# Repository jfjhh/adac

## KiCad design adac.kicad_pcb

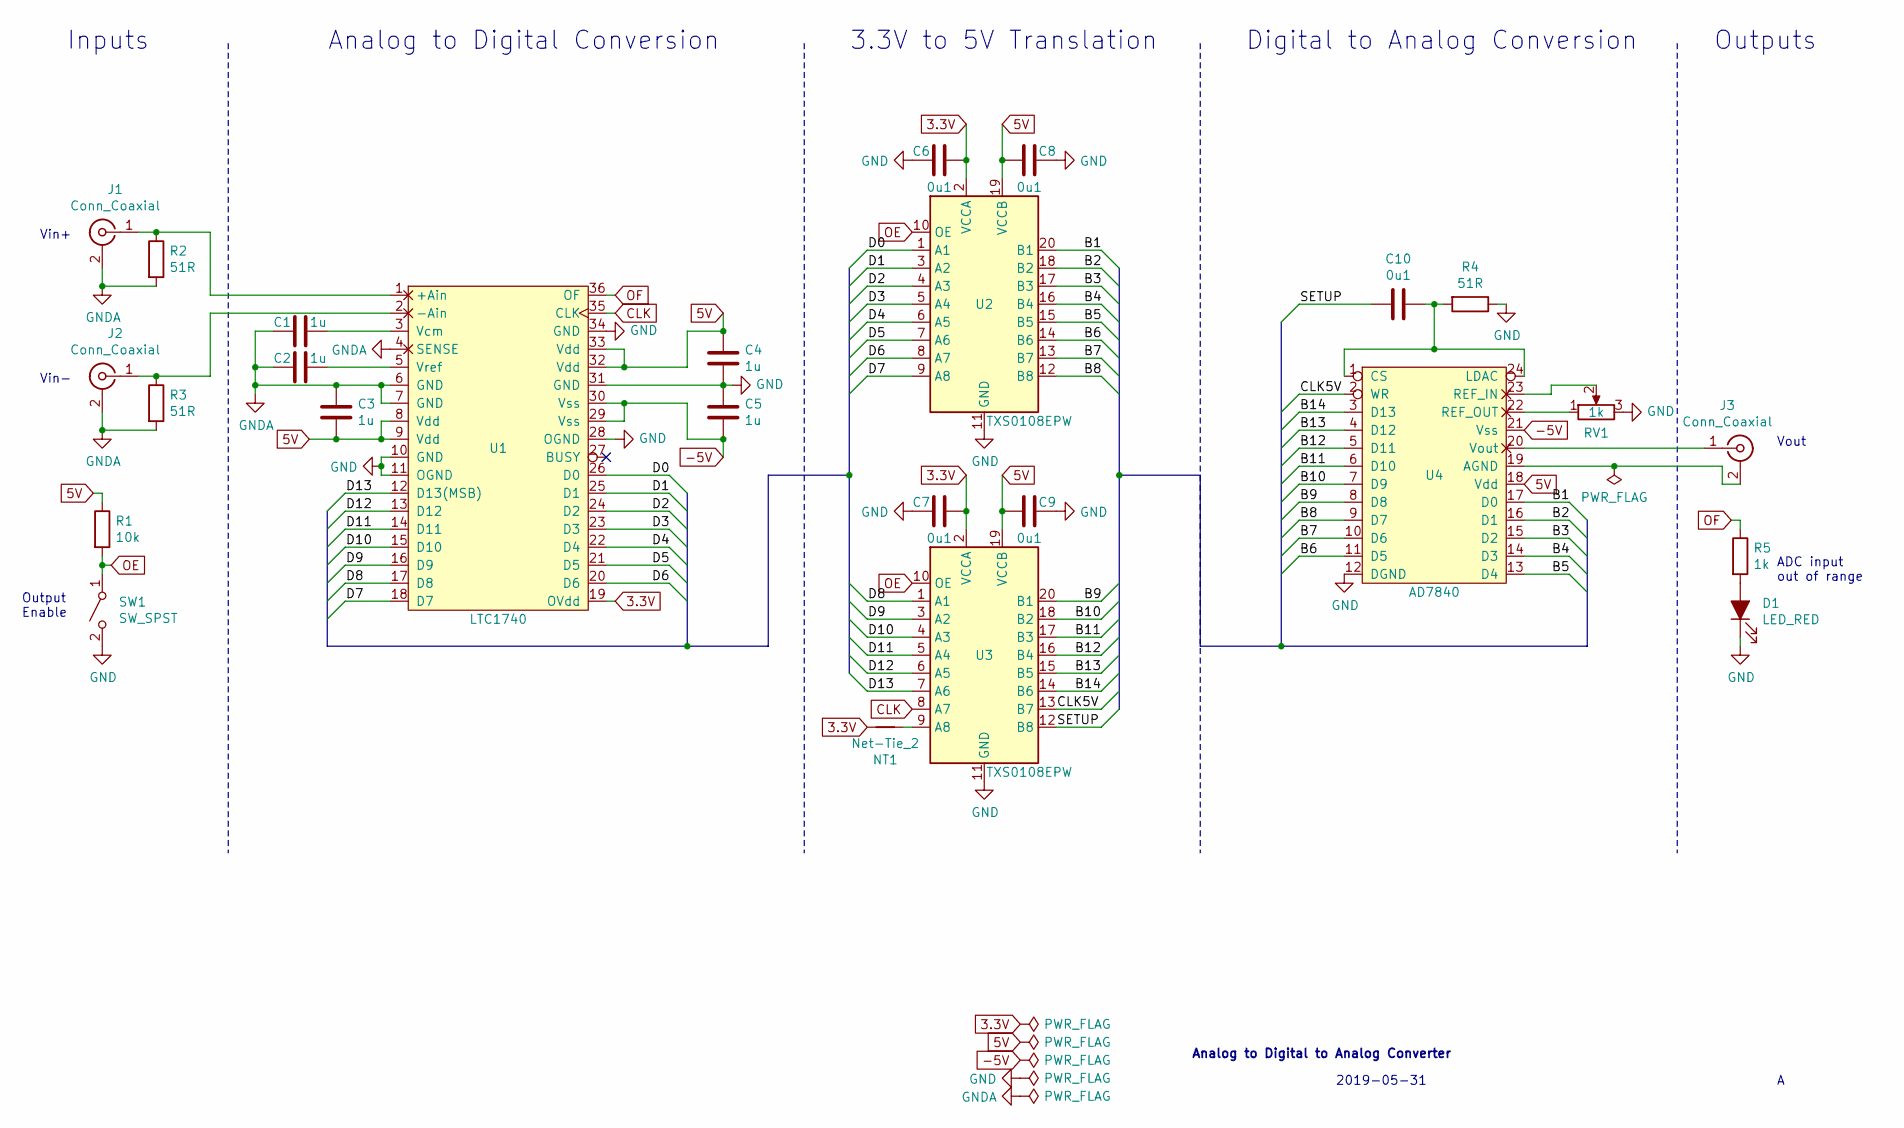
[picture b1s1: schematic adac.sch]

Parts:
C1, C2, C3, C4, C5: 1u; C_Disc_D3.4mm_W2.1mm_P2.50mm
C6, C7, C8, C9, C10: 0u1; C_Disc_D3.4mm_W2.1mm_P2.50mm
D1: LED_RED; LED_D3.0mm
J1, J2, J3: Conn_Coaxial; BNC_TEConnectivity_1478204_Vertical
NT1: Net-Tie_2; NetTie-2_SMD_Pad0.5mm
R1: 10k; R_Axial_DIN0204_L3.6mm_D1.6mm_P7.62mm_Horizontal
R2, R3, R4: 51R; R_Axial_DIN0204_L3.6mm_D1.6mm_P7.62mm_Horizontal
R5: 1k; R_Axial_DIN0204_L3.6mm_D1.6mm_P7.62mm_Horizontal
RV1: 1k; Potentiometer_Bourns_3296W_Vertical
SW1: SW_SPST; SW_CuK_JS202011CQN_DPDT_Straight
U1: LTC1740; SSOP-44_5.3x12.8mm_P0.5mm
U2, U3: TXS0108EPW; TSSOP-20_4.4x6.5mm_P0.65mm
U4: AD7840; DIP-24_W7.62mm_LongPads

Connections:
3.3V: C6.1, C7.1, NT1.2, U1.19 (OVdd), U2.2 (VCCA), U3.2 (VCCA)
5V: C3.2, C4.1, C8.1, C9.1, R1.1, U1.8 (Vdd), U1.9 (Vdd), U1.32 (Vdd), U1.33 (Vdd), U2.19 (VCCB), U3.19 (VCCB), U4.18 (Vdd)
-5V: C5.2, U1.29 (Vss), U1.30 (Vss), U4.21 (Vss)
/B1: U2.20 (B1), U4.17 (D0)
/B2: U2.18 (B2), U4.16 (D1)
/B3: U2.17 (B3), U4.15 (D2)
/B4: U2.16 (B4), U4.14 (D3)
/B5: U2.15 (B5), U4.13 (D4)
/B6: U2.14 (B6), U4.11 (D5)
/B7: U2.13 (B7), U4.10 (D6)
/B8: U2.12 (B8), U4.9 (D7)
/B9: U3.20 (B1), U4.8 (D8)
/B10: U3.18 (B2), U4.7 (D9)
/B11: U3.17 (B3), U4.6 (D10)
/B12: U3.16 (B4), U4.5 (D11)
/B13: U3.15 (B5), U4.4 (D12)
/B14: U3.14 (B6), U4.3 (D13)
/CLK5V: U3.13 (B7), U4.2 (WR)
/D0: U1.26 (D0), U2.1 (A1)
/D1: U1.25 (D1), U2.3 (A2)
/D2: U1.24 (D2), U2.4 (A3)
/D3: U1.23 (D3), U2.5 (A4)
/D4: U1.22 (D4), U2.6 (A5)
/D5: U1.21 (D5), U2.7 (A6)
/D6: U1.20 (D6), U2.8 (A7)
/D7: U1.18 (D7), U2.9 (A8)
/D8: U1.17 (D8), U3.1 (A1)
/D9: U1.16 (D9), U3.3 (A2)
/D10: U1.15 (D10), U3.4 (A3)
/D11: U1.14 (D11), U3.5 (A4)
/D12: U1.13 (D12), U3.6 (A5)
/D13: U1.12 (D13(MSB)), U3.7 (A6)
/SETUP: C10.2, U3.12 (B8)
CLK: U1.35 (CLK), U3.8 (A7)
GND: C4.2, C5.1, C6.2, C7.2, C8.2, C9.2, D1.1 (K), R4.1, RV1.3, SW1.2 (B), U1.10 (GND), U1.11 (OGND), U1.28 (OGND), U1.31 (GND), U1.34 (GND), U2.11 (GND), U3.11 (GND), U4.12 (DGND)
GNDA: C1.2, C2.2, C3.1, J1.2 (Ext), J2.2 (Ext), R2.2, R3.2, U1.4 (SENSE), U1.6 (GND), U1.7 (GND)
unnamed: C1.1, U1.3 (Vcm)
unnamed: C2.1, U1.5 (Vref)
unnamed: C10.1, R4.2, U4.1 (CS), U4.24 (LDAC)
unnamed: D1.2 (A), R5.2
unnamed: J1.1 (In), R2.1, U1.1 (+Ain)
unnamed: J2.1 (In), R3.1, U1.2 (-Ain)
unnamed: J3.1 (In), U4.20 (Vout)
unnamed: J3.2 (Ext), U4.19 (AGND)
unnamed: NT1.1, U3.9 (A8)
unnamed: RV1.1, U4.22 (REF_OUT)
unnamed: RV1.2, U4.23 (REF_IN)
OE: R1.2, SW1.1 (A), U2.10 (OE), U3.10 (OE)
OF: R5.1, U1.36 (OF)

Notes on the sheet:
Analog to Digital to Analog Converter
2019-05-31
Inputs
Analog to Digital Conversion
3.3V to 5V Translation
Digital to Analog Conversion
Outputs
Vout
Vin+
Vin-
Output Enable
ADC input out of range

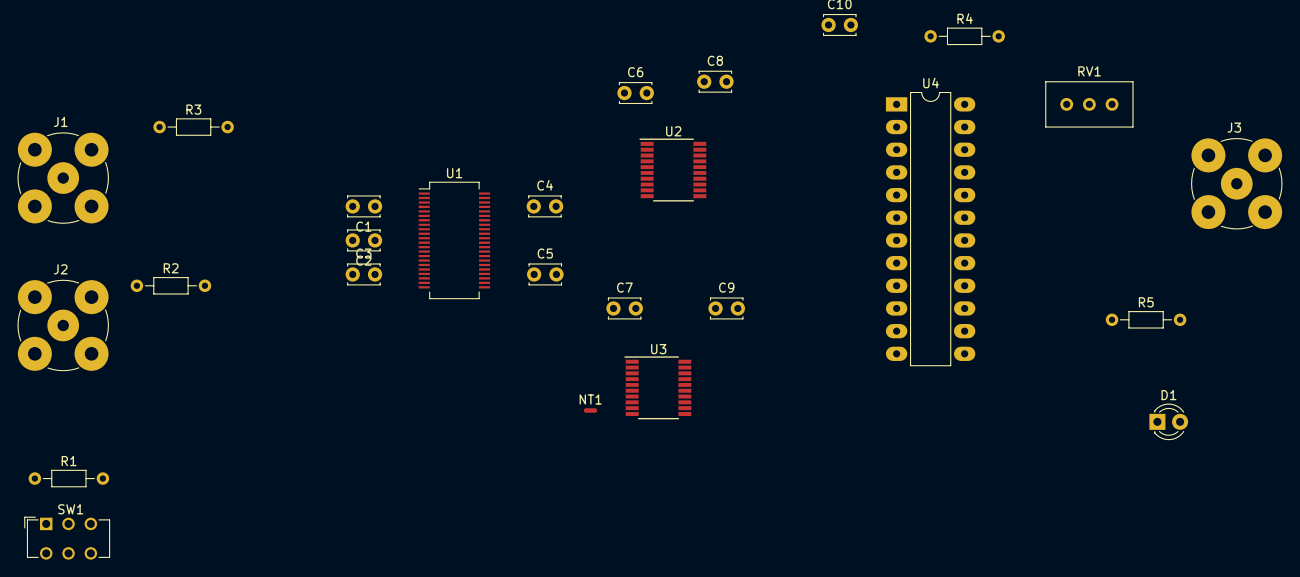
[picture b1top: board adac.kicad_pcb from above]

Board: 2 copper layers, 26 parts (0 on the bottom side), 49 nets.

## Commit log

2019-05-31 Add KiCad files
    Partial progress. Still need to figure out the DAC initialization.
2019-05-31 Rev A complete
    Added initialization for the DAC and other minor changes.
2019-05-31 Added power flags to pass ERC
2019-05-31 Added footprints
2019-05-31 Spread out components
2019-05-31 Add clock input connector
